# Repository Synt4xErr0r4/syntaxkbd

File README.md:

# syntaxkbd

A keyboard I made a while back.

Uses Kailh hotswap sockets with Kailh White Box V2 switches.
Standard UK QWERTY layout with 5 additional macro keys on the left (the ones where the keycaps are missing in the image below).

Also has an SK6812MINI-E addressable RGB LED for each key.

There are also four indicator LEDs (NumLock, CapsLock, ScrollLock, WinLock).
Originally, I intended to use a shift register and four discrete LEDs, but I messed up somewhere, so I bodged a WS2812B LED strip there instead.

The keycaps in the picture are from the ASUS ROG PBT Keycap Set.

The keyboard is connected via USB-C to an RP2354B microcontroller (and probably exceeds the USB standard's maximum allowed VBUS capacitance!).

The case you can see in the first image was 3D printed (PETG) in four parts.

The key placement for the PCB was done with a KiCAD extension (don't remember which one).

The keyboard is split into two PCBs: one for the keys and LEDs, and one for the controller.

Both PCBs were manufactured by JLCPCB.
I assembled the keyboard PCB (2-layer) myself, but I let JLC assemble the controller PCB (4-layer) because of the fine-pitched pins of the RP2354B.

Since the controller is an RP2354B, it can be programmed using a Raspberry Pi Debug Probe (using the SWD connector), and the firmware is written using the Raspberry Pi SDK.

I'm not quite sure what the problem is, but when I have RGB lighting effects running for a while, it starts glitching, so I usually have the LED set to static white.

Also, the firmware is not finished yet, so macros don't work yet, and lighting effects can only be reconfigured by recompiling the firmware.
It's most likely full of bugs too.
In the future, I'm also planning to have a program that can communicate with the keyboard using a vendor-specific USB interface to configure lighting effects and macros and so on.

Nonetheless, I've been using it daily for about half a year now, and it's been working great so far!

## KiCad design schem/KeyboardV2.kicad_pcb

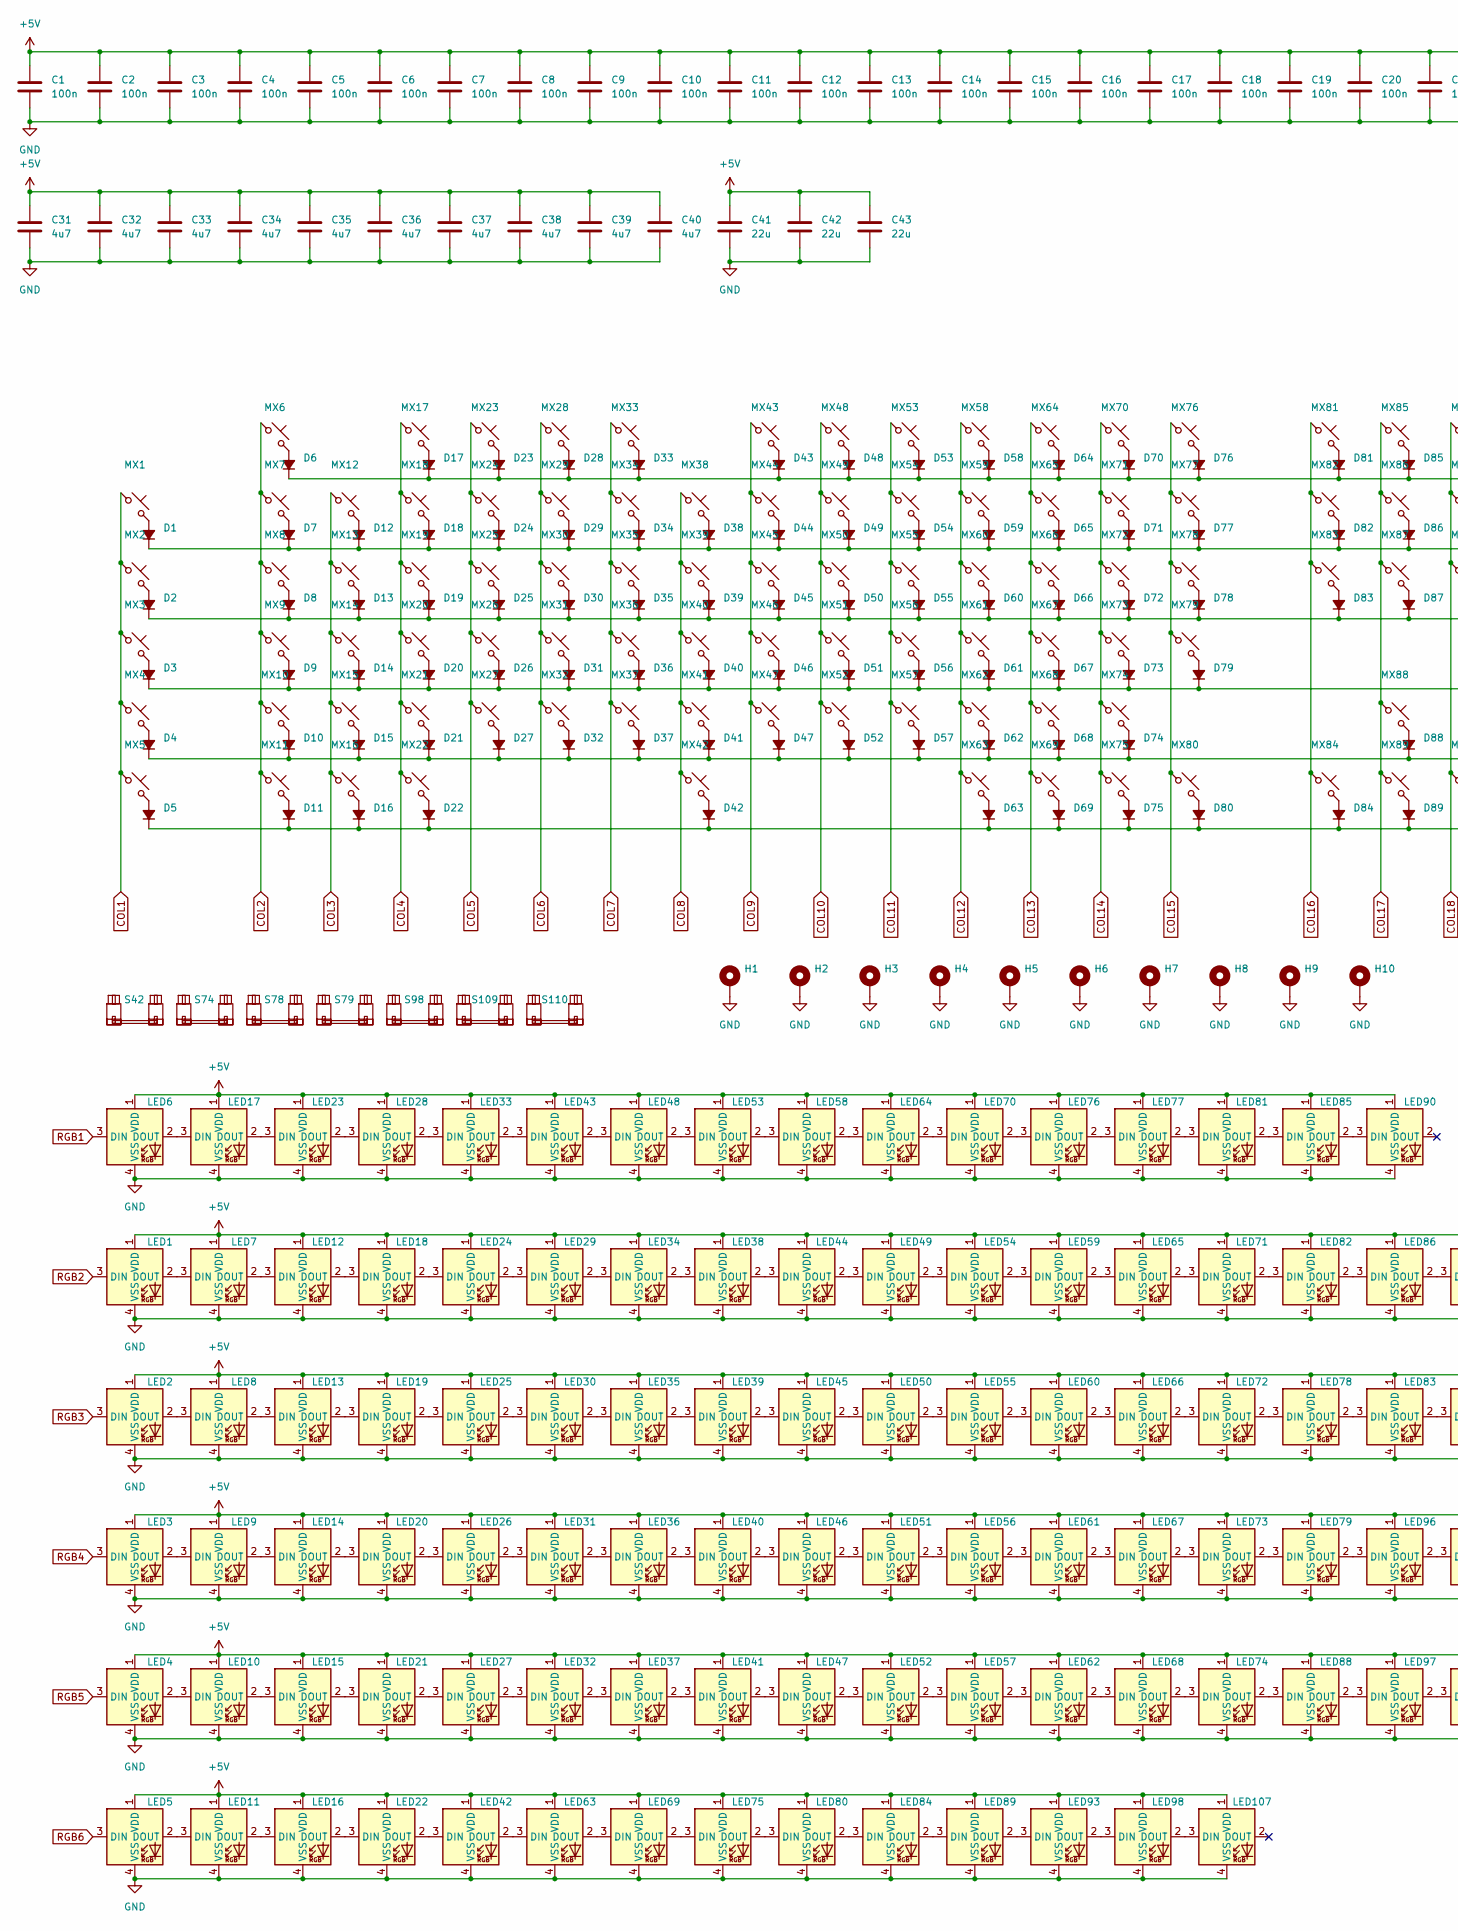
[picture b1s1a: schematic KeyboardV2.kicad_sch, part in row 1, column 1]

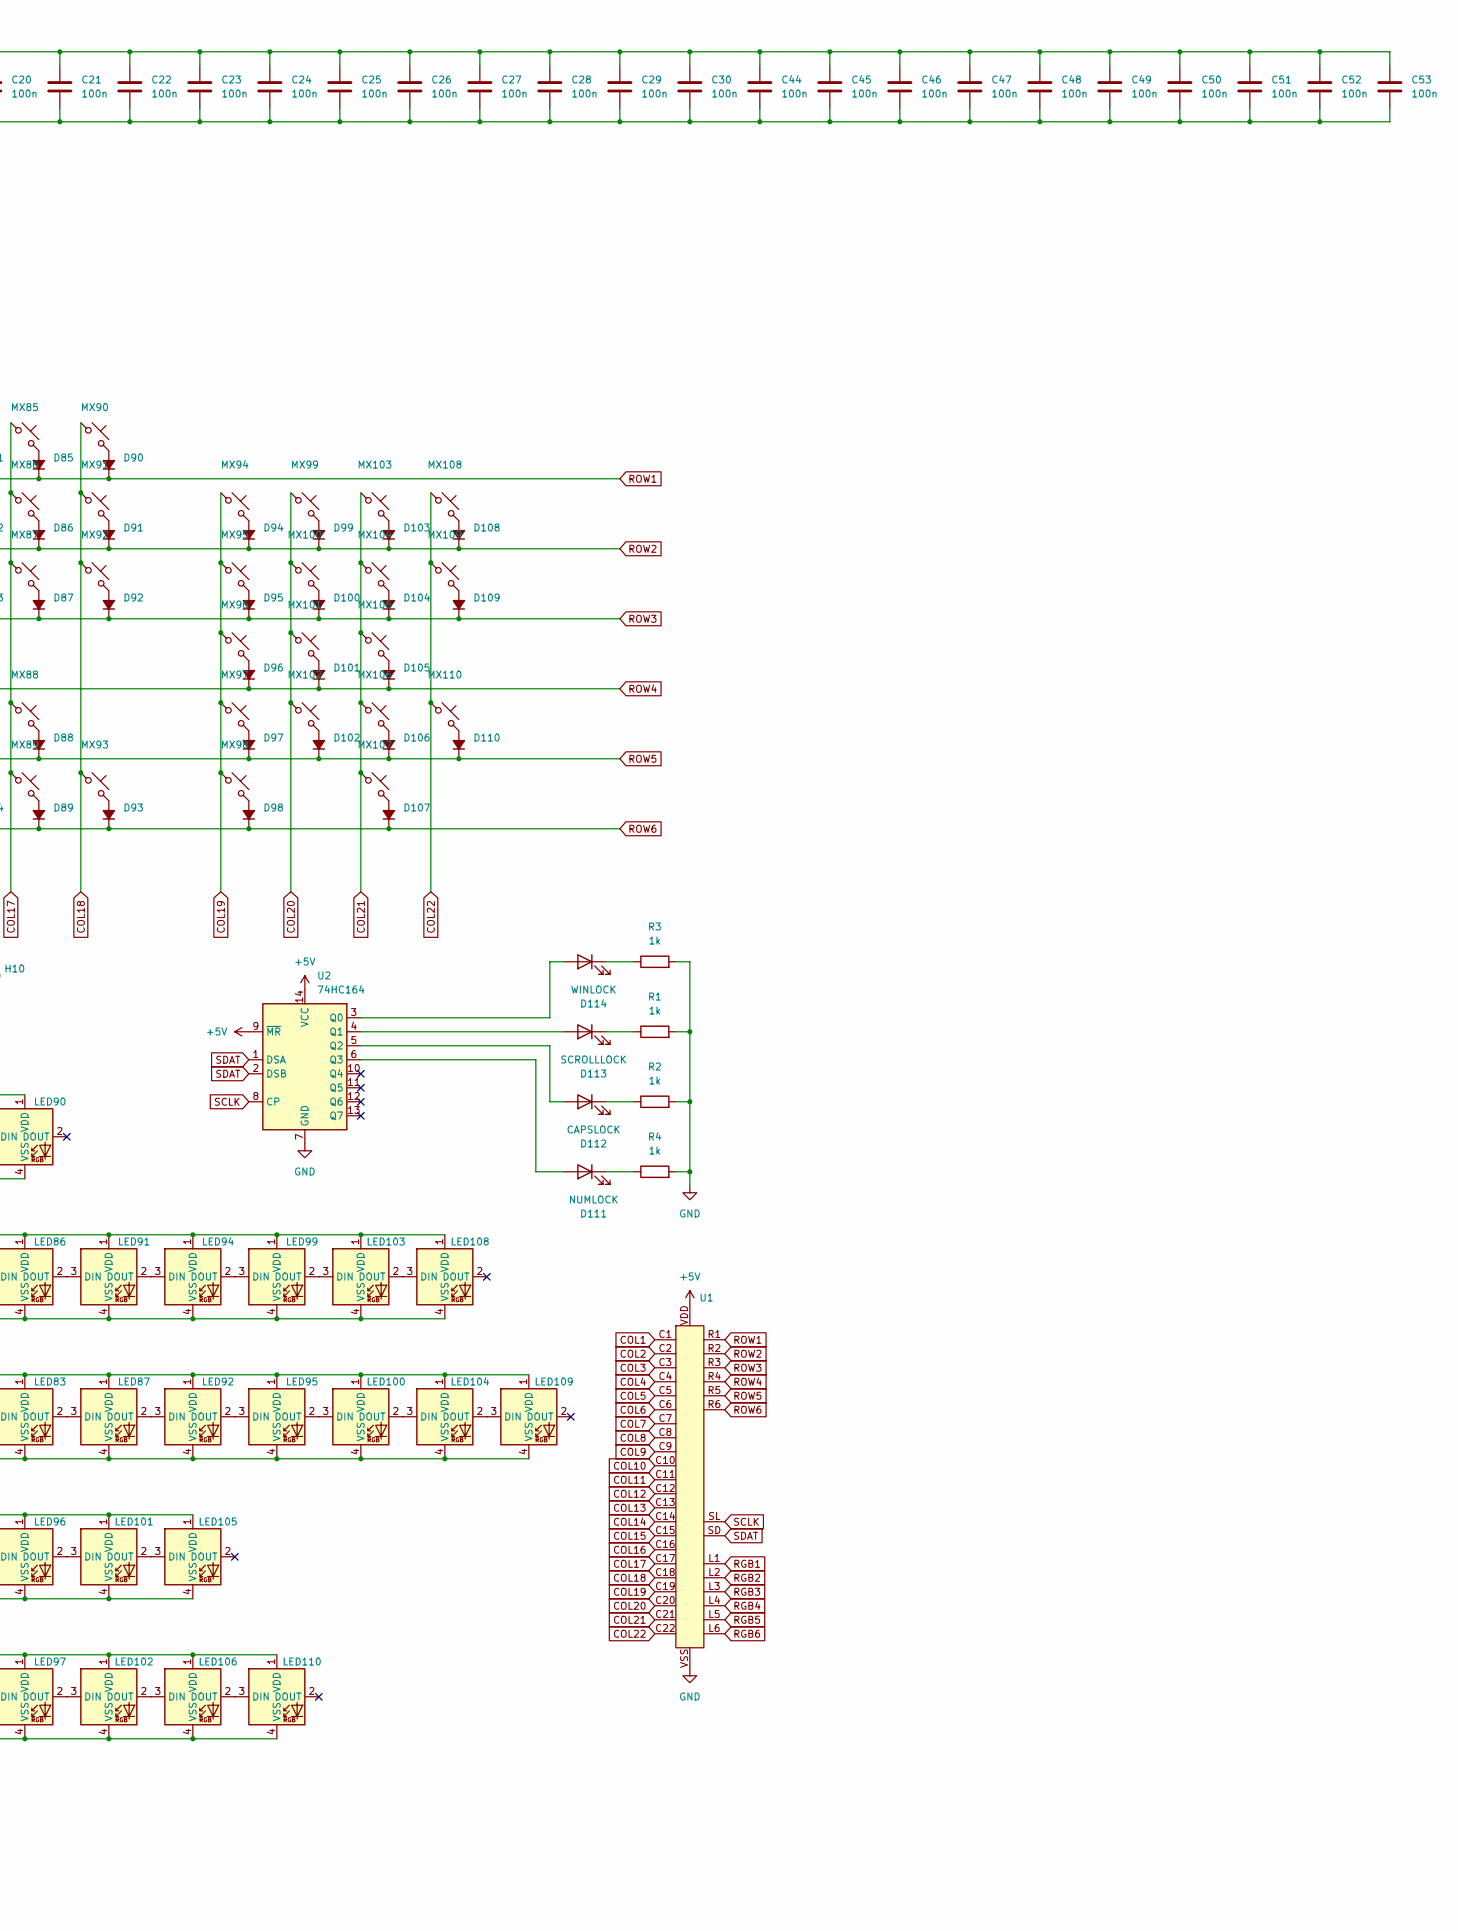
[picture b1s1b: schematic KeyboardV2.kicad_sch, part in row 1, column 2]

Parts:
C1, C2, C3, C4, C5, C6, C7, C8, C9, C10, C11, C12, C13, C14, C15, C16, C17, C18, C19, C20, C21, C22, C23, C24, C25, C26, C27, C28, C29, C30, C44, C45, C46, C47, C48, C49, C50, C51, C52, C53: 100n; C_0805_2012Metric_Pad1.18x1.45mm_HandSolder
C31, C32, C33, C34, C35, C36, C37, C38, C39, C40: 4u7; C_0805_2012Metric_Pad1.18x1.45mm_HandSolder
C41, C42, C43: 22u; C_0805_2012Metric_Pad1.18x1.45mm_HandSolder
D1, D2, D3, D4, D5, D6, D7, D8, D9, D10, D11, D12, D13, D14, D15, D16, D17, D18, D19, D20, D21, D22, D23, D24, D25, D26, D27, D28, D29, D30, D31, D32, D33, D34, D35, D36, D37, D38, D39, D40, D41, D42, D43, D44, D45, D46, D47, D48, D49, D50, D51, D52, D53, D54, D55, D56, D57, D58, D59, D60, D61, D62, D63, D64, D65, D66, D67, D68, D69, D70, D71, D72, D73, D74, D75, D76, D77, D78, D79, D80, D81, D82, D83, D84, D85, D86, D87, D88, D89, D90, D91, D92, D93, D94, D95, D96, D97, D98, D99, D100, D101, D102, D103, D104, D105, D106, D107, D108, D109, D110: D_SOD-323_HandSoldering
D111: NUMLOCK; LED_PLCC-2_3.4x3.0mm_AK
D112: CAPSLOCK; LED_PLCC-2_3.4x3.0mm_AK
D113: SCROLLLOCK; LED_PLCC-2_3.4x3.0mm_AK
D114: WINLOCK; LED_PLCC-2_3.4x3.0mm_AK
H1, H2, H3, H4, H5, H6, H7, H8, H9, H10: MountingHole_Pad; MountingHole_3.2mm_M3_DIN965_Pad_TopBottom
LED1, LED2, LED3, LED4, LED5, LED6, LED7, LED8, LED9, LED10, LED11, LED12, LED13, LED14, LED15, LED16, LED17, LED18, LED19, LED20, LED21, LED22, LED23, LED24, LED25, LED26, LED27, LED28, LED29, LED30, LED31, LED32, LED33, LED34, LED35, LED36, LED37, LED38, LED39, LED40, LED41, LED42, LED43, LED44, LED45, LED46, LED47, LED48, LED49, LED50, LED51, LED52, LED53, LED54, LED55, LED56, LED57, LED58, LED59, LED60, LED61, LED62, LED63, LED64, LED65, LED66, LED67, LED68, LED69, LED70, LED71, LED72, LED73, LED74, LED75, LED76, LED77, LED78, LED79, LED80, LED81, LED82, LED83, LED84, LED85, LED86, LED87, LED88, LED89, LED90, LED91, LED92, LED93, LED94, LED95, LED96, LED97, LED98, LED99, LED100, LED101, LED102, LED103, LED104, LED105, LED106, LED107, LED108, LED109, LED110: MX_SK6812MINI-E; LED_MX_6028R
MX1, MX2, MX3, MX4, MX5, MX6, MX7, MX8, MX9, MX10, MX11, MX12, MX13, MX14, MX15, MX16, MX17, MX18, MX19, MX20, MX21, MX22, MX23, MX24, MX25, MX26, MX27, MX28, MX29, MX30, MX31, MX32, MX33, MX34, MX35, MX36, MX37, MX38, MX39, MX40, MX41, MX42, MX43, MX44, MX45, MX46, MX47, MX48, MX49, MX50, MX51, MX52, MX53, MX54, MX55, MX56, MX57, MX58, MX59, MX60, MX61, MX62, MX63, MX64, MX65, MX66, MX67, MX68, MX69, MX70, MX71, MX72, MX73, MX74, MX75, MX76, MX77, MX78, MX79, MX80, MX81, MX82, MX83, MX84, MX85, MX86, MX87, MX88, MX89, MX90, MX91, MX92, MX93, MX94, MX95, MX96, MX97, MX98, MX99, MX100, MX101, MX102, MX103, MX104, MX105, MX106, MX107, MX108, MX109, MX110: SW_MX_HS_CPG151101S11_1u
R1, R2, R3, R4: 1k; R_0402_1005Metric_Pad0.72x0.64mm_HandSolder
S42: MX_stab; STAB_MX_P_6.25u
S74: MX_stab; STAB_MX_P_2.75u
S78, S98, S109, S110: MX_stab; STAB_MX_P_2u
S79: MX_stab; STAB_MX_P_ISO
U1: KBDCTRL_Conn
U2: 74HC164; SOIC-14_3.9x8.7mm_P1.27mm

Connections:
+5V: C1.1, C2.1, C3.1, C4.1, C5.1, C6.1, C7.1, C8.1, C9.1, C10.1, C11.1, C12.1, C13.1, C14.1, C15.1, C16.1, C17.1, C18.1, C19.1, C20.1, C21.1, C22.1, C23.1, C24.1, C25.1, C26.1, C27.1, C28.1, C29.1, C30.1, C31.1, C32.1, C33.1, C34.1, C35.1, C36.1, C37.1, C38.1, C39.1, C40.1, C41.1, C42.1, C43.1, C44.1, C45.1, C46.1, C47.1, C48.1, C49.1, C50.1, C51.1, C52.1, C53.1, LED1.1 (VDD), LED2.1 (VDD), LED3.1 (VDD), LED4.1 (VDD), LED5.1 (VDD), LED6.1 (VDD), LED7.1 (VDD), LED8.1 (VDD), LED9.1 (VDD), LED10.1 (VDD), LED11.1 (VDD), LED12.1 (VDD), LED13.1 (VDD), LED14.1 (VDD), LED15.1 (VDD), LED16.1 (VDD), LED17.1 (VDD), LED18.1 (VDD), LED19.1 (VDD), LED20.1 (VDD), LED21.1 (VDD), LED22.1 (VDD), LED23.1 (VDD), LED24.1 (VDD), LED25.1 (VDD), LED26.1 (VDD), LED27.1 (VDD), LED28.1 (VDD), LED29.1 (VDD), LED30.1 (VDD), LED31.1 (VDD), LED32.1 (VDD), LED33.1 (VDD), LED34.1 (VDD), LED35.1 (VDD), LED36.1 (VDD), LED37.1 (VDD), LED38.1 (VDD), LED39.1 (VDD), LED40.1 (VDD), LED41.1 (VDD), LED42.1 (VDD), LED43.1 (VDD), LED44.1 (VDD), LED45.1 (VDD), LED46.1 (VDD), LED47.1 (VDD), LED48.1 (VDD), LED49.1 (VDD), LED50.1 (VDD), LED51.1 (VDD), LED52.1 (VDD), LED53.1 (VDD), LED54.1 (VDD), LED55.1 (VDD), LED56.1 (VDD), LED57.1 (VDD), LED58.1 (VDD), LED59.1 (VDD), LED60.1 (VDD), LED61.1 (VDD), LED62.1 (VDD), LED63.1 (VDD), LED64.1 (VDD), LED65.1 (VDD), LED66.1 (VDD), LED67.1 (VDD), LED68.1 (VDD), LED69.1 (VDD), LED70.1 (VDD), LED71.1 (VDD), LED72.1 (VDD), LED73.1 (VDD), LED74.1 (VDD), LED75.1 (VDD), LED76.1 (VDD), LED77.1 (VDD), LED78.1 (VDD), LED79.1 (VDD), LED80.1 (VDD), LED81.1 (VDD), LED82.1 (VDD), LED83.1 (VDD), LED84.1 (VDD), LED85.1 (VDD), LED86.1 (VDD), LED87.1 (VDD), LED88.1 (VDD), LED89.1 (VDD), LED90.1 (VDD), LED91.1 (VDD), LED92.1 (VDD), LED93.1 (VDD), LED94.1 (VDD), LED95.1 (VDD), LED96.1 (VDD), LED97.1 (VDD), LED98.1 (VDD), LED99.1 (VDD), LED100.1 (VDD), LED101.1 (VDD), LED102.1 (VDD), LED103.1 (VDD), LED104.1 (VDD), LED105.1 (VDD), LED106.1 (VDD), LED107.1 (VDD), LED108.1 (VDD), LED109.1 (VDD), LED110.1 (VDD), U1.VDD, U2.9 (~MR), U2.14 (VCC)
COL1: MX1.1, MX2.1, MX3.1, MX4.1, MX5.1, U1.C1
COL2: MX6.1, MX7.1, MX8.1, MX9.1, MX10.1, MX11.1, U1.C2
COL3: MX12.1, MX13.1, MX14.1, MX15.1, MX16.1, U1.C3
COL4: MX17.1, MX18.1, MX19.1, MX20.1, MX21.1, MX22.1, U1.C4
COL5: MX23.1, MX24.1, MX25.1, MX26.1, MX27.1, U1.C5
COL6: MX28.1, MX29.1, MX30.1, MX31.1, MX32.1, U1.C6
COL7: MX33.1, MX34.1, MX35.1, MX36.1, MX37.1, U1.C7
COL8: MX38.1, MX39.1, MX40.1, MX41.1, MX42.1, U1.C8
COL9: MX43.1, MX44.1, MX45.1, MX46.1, MX47.1, U1.C9
COL10: MX48.1, MX49.1, MX50.1, MX51.1, MX52.1, U1.C10
COL11: MX53.1, MX54.1, MX55.1, MX56.1, MX57.1, U1.C11
COL12: MX58.1, MX59.1, MX60.1, MX61.1, MX62.1, MX63.1, U1.C12
COL13: MX64.1, MX65.1, MX66.1, MX67.1, MX68.1, MX69.1, U1.C13
COL14: MX70.1, MX71.1, MX72.1, MX73.1, MX74.1, MX75.1, U1.C14
COL15: MX76.1, MX77.1, MX78.1, MX79.1, MX80.1, U1.C15
COL16: MX81.1, MX82.1, MX83.1, MX84.1, U1.C16
COL17: MX85.1, MX86.1, MX87.1, MX88.1, MX89.1, U1.C17
COL18: MX90.1, MX91.1, MX92.1, MX93.1, U1.C18
COL19: MX94.1, MX95.1, MX96.1, MX97.1, MX98.1, U1.C19
COL20: MX99.1, MX100.1, MX101.1, MX102.1, U1.C20
COL21: MX103.1, MX104.1, MX105.1, MX106.1, MX107.1, U1.C21
COL22: MX108.1, MX109.1, MX110.1, U1.C22
GND: C1.2, C2.2, C3.2, C4.2, C5.2, C6.2, C7.2, C8.2, C9.2, C10.2, C11.2, C12.2, C13.2, C14.2, C15.2, C16.2, C17.2, C18.2, C19.2, C20.2, C21.2, C22.2, C23.2, C24.2, C25.2, C26.2, C27.2, C28.2, C29.2, C30.2, C31.2, C32.2, C33.2, C34.2, C35.2, C36.2, C37.2, C38.2, C39.2, C40.2, C41.2, C42.2, C43.2, C44.2, C45.2, C46.2, C47.2, C48.2, C49.2, C50.2, C51.2, C52.2, C53.2, H1.1, H2.1, H3.1, H4.1, H5.1, H6.1, H7.1, H8.1, H9.1, H10.1, LED1.4 (VSS), LED2.4 (VSS), LED3.4 (VSS), LED4.4 (VSS), LED5.4 (VSS), LED6.4 (VSS), LED7.4 (VSS), LED8.4 (VSS), LED9.4 (VSS), LED10.4 (VSS), LED11.4 (VSS), LED12.4 (VSS), LED13.4 (VSS), LED14.4 (VSS), LED15.4 (VSS), LED16.4 (VSS), LED17.4 (VSS), LED18.4 (VSS), LED19.4 (VSS), LED20.4 (VSS), LED21.4 (VSS), LED22.4 (VSS), LED23.4 (VSS), LED24.4 (VSS), LED25.4 (VSS), LED26.4 (VSS), LED27.4 (VSS), LED28.4 (VSS), LED29.4 (VSS), LED30.4 (VSS), LED31.4 (VSS), LED32.4 (VSS), LED33.4 (VSS), LED34.4 (VSS), LED35.4 (VSS), LED36.4 (VSS), LED37.4 (VSS), LED38.4 (VSS), LED39.4 (VSS), LED40.4 (VSS), LED41.4 (VSS), LED42.4 (VSS), LED43.4 (VSS), LED44.4 (VSS), LED45.4 (VSS), LED46.4 (VSS), LED47.4 (VSS), LED48.4 (VSS), LED49.4 (VSS), LED50.4 (VSS), LED51.4 (VSS), LED52.4 (VSS), LED53.4 (VSS), LED54.4 (VSS), LED55.4 (VSS), LED56.4 (VSS), LED57.4 (VSS), LED58.4 (VSS), LED59.4 (VSS), LED60.4 (VSS), LED61.4 (VSS), LED62.4 (VSS), LED63.4 (VSS), LED64.4 (VSS), LED65.4 (VSS), LED66.4 (VSS), LED67.4 (VSS), LED68.4 (VSS), LED69.4 (VSS), LED70.4 (VSS), LED71.4 (VSS), LED72.4 (VSS), LED73.4 (VSS), LED74.4 (VSS), LED75.4 (VSS), LED76.4 (VSS), LED77.4 (VSS), LED78.4 (VSS), LED79.4 (VSS), LED80.4 (VSS), LED81.4 (VSS), LED82.4 (VSS), LED83.4 (VSS), LED84.4 (VSS), LED85.4 (VSS), LED86.4 (VSS), LED87.4 (VSS), LED88.4 (VSS), LED89.4 (VSS), LED90.4 (VSS), LED91.4 (VSS), LED92.4 (VSS), LED93.4 (VSS), LED94.4 (VSS), LED95.4 (VSS), LED96.4 (VSS), LED97.4 (VSS), LED98.4 (VSS), LED99.4 (VSS), LED100.4 (VSS), LED101.4 (VSS), LED102.4 (VSS), LED103.4 (VSS), LED104.4 (VSS), LED105.4 (VSS), LED106.4 (VSS), LED107.4 (VSS), LED108.4 (VSS), LED109.4 (VSS), LED110.4 (VSS), R1.2, R2.2, R3.2, R4.2, U1.VSS, U2.7 (GND)
unnamed: D1.2 (A), MX1.2
unnamed: D2.2 (A), MX2.2
unnamed: D3.2 (A), MX3.2
unnamed: D4.2 (A), MX4.2
unnamed: D5.2 (A), MX5.2
unnamed: D6.2 (A), MX6.2
unnamed: D7.2 (A), MX7.2
unnamed: D8.2 (A), MX8.2
unnamed: D9.2 (A), MX9.2
unnamed: D10.2 (A), MX10.2
unnamed: D11.2 (A), MX11.2
unnamed: D12.2 (A), MX12.2
unnamed: D13.2 (A), MX13.2
unnamed: D14.2 (A), MX14.2
unnamed: D15.2 (A), MX15.2
unnamed: D16.2 (A), MX16.2
unnamed: D17.2 (A), MX17.2
unnamed: D18.2 (A), MX18.2
unnamed: D19.2 (A), MX19.2
unnamed: D20.2 (A), MX20.2
unnamed: D21.2 (A), MX21.2
unnamed: D22.2 (A), MX22.2
unnamed: D23.2 (A), MX23.2
unnamed: D24.2 (A), MX24.2
unnamed: D25.2 (A), MX25.2
unnamed: D26.2 (A), MX26.2
unnamed: D27.2 (A), MX27.2
unnamed: D28.2 (A), MX28.2
unnamed: D29.2 (A), MX29.2
unnamed: D30.2 (A), MX30.2
unnamed: D31.2 (A), MX31.2
unnamed: D32.2 (A), MX32.2
unnamed: D33.2 (A), MX33.2
unnamed: D34.2 (A), MX34.2
unnamed: D35.2 (A), MX35.2
unnamed: D36.2 (A), MX36.2
unnamed: D37.2 (A), MX37.2
unnamed: D38.2 (A), MX38.2
unnamed: D39.2 (A), MX39.2
unnamed: D40.2 (A), MX40.2
unnamed: D41.2 (A), MX41.2
unnamed: D42.2 (A), MX42.2
unnamed: D43.2 (A), MX43.2
unnamed: D44.2 (A), MX44.2
unnamed: D45.2 (A), MX45.2
unnamed: D46.2 (A), MX46.2
unnamed: D47.2 (A), MX47.2
unnamed: D48.2 (A), MX48.2
unnamed: D49.2 (A), MX49.2
unnamed: D50.2 (A), MX50.2
unnamed: D51.2 (A), MX51.2
unnamed: D52.2 (A), MX52.2
unnamed: D53.2 (A), MX53.2
unnamed: D54.2 (A), MX54.2
unnamed: D55.2 (A), MX55.2
unnamed: D56.2 (A), MX56.2
unnamed: D57.2 (A), MX57.2
unnamed: D58.2 (A), MX58.2
unnamed: D59.2 (A), MX59.2
unnamed: D60.2 (A), MX60.2
unnamed: D61.2 (A), MX61.2
unnamed: D62.2 (A), MX62.2
unnamed: D63.2 (A), MX63.2
unnamed: D64.2 (A), MX64.2
unnamed: D65.2 (A), MX65.2
unnamed: D66.2 (A), MX66.2
unnamed: D67.2 (A), MX67.2
unnamed: D68.2 (A), MX68.2
unnamed: D69.2 (A), MX69.2
unnamed: D70.2 (A), MX70.2
unnamed: D71.2 (A), MX71.2
unnamed: D72.2 (A), MX72.2
unnamed: D73.2 (A), MX73.2
unnamed: D74.2 (A), MX74.2
unnamed: D75.2 (A), MX75.2
unnamed: D76.2 (A), MX76.2
unnamed: D77.2 (A), MX77.2
unnamed: D78.2 (A), MX78.2
unnamed: D79.2 (A), MX79.2
unnamed: D80.2 (A), MX80.2
unnamed: D81.2 (A), MX81.2
unnamed: D82.2 (A), MX82.2
unnamed: D83.2 (A), MX83.2
unnamed: D84.2 (A), MX84.2
unnamed: D85.2 (A), MX85.2
unnamed: D86.2 (A), MX86.2
unnamed: D87.2 (A), MX87.2
unnamed: D88.2 (A), MX88.2
unnamed: D89.2 (A), MX89.2
unnamed: D90.2 (A), MX90.2
unnamed: D91.2 (A), MX91.2
unnamed: D92.2 (A), MX92.2
unnamed: D93.2 (A), MX93.2
unnamed: D94.2 (A), MX94.2
unnamed: D95.2 (A), MX95.2
unnamed: D96.2 (A), MX96.2
unnamed: D97.2 (A), MX97.2
unnamed: D98.2 (A), MX98.2
unnamed: D99.2 (A), MX99.2
unnamed: D100.2 (A), MX100.2
unnamed: D101.2 (A), MX101.2
unnamed: D102.2 (A), MX102.2
unnamed: D103.2 (A), MX103.2
unnamed: D104.2 (A), MX104.2
unnamed: D105.2 (A), MX105.2
unnamed: D106.2 (A), MX106.2
unnamed: D107.2 (A), MX107.2
unnamed: D108.2 (A), MX108.2
unnamed: D109.2 (A), MX109.2
unnamed: D110.2 (A), MX110.2
unnamed: D111.2 (A), U2.6 (Q3)
unnamed: D111.1 (K), R4.1
unnamed: D112.2 (A), U2.5 (Q2)
unnamed: D112.1 (K), R2.1
unnamed: D113.2 (A), U2.4 (Q1)
unnamed: D113.1 (K), R1.1
unnamed: D114.2 (A), U2.3 (Q0)
unnamed: D114.1 (K), R3.1
unnamed: LED1.2 (DOUT), LED7.3 (DIN)
unnamed: LED2.2 (DOUT), LED8.3 (DIN)
unnamed: LED3.2 (DOUT), LED9.3 (DIN)
unnamed: LED4.2 (DOUT), LED10.3 (DIN)
unnamed: LED10.2 (DOUT), LED15.3 (DIN)
unnamed: LED5.2 (DOUT), LED11.3 (DIN)
unnamed: LED11.2 (DOUT), LED16.3 (DIN)
unnamed: LED7.2 (DOUT), LED12.3 (DIN)
unnamed: LED12.2 (DOUT), LED18.3 (DIN)
unnamed: LED8.2 (DOUT), LED13.3 (DIN)
unnamed: LED13.2 (DOUT), LED19.3 (DIN)
unnamed: LED9.2 (DOUT), LED14.3 (DIN)
unnamed: LED14.2 (DOUT), LED20.3 (DIN)
unnamed: LED15.2 (DOUT), LED21.3 (DIN)
unnamed: LED16.2 (DOUT), LED22.3 (DIN)
unnamed: LED6.2 (DOUT), LED17.3 (DIN)
unnamed: LED17.2 (DOUT), LED23.3 (DIN)
unnamed: LED18.2 (DOUT), LED24.3 (DIN)
unnamed: LED19.2 (DOUT), LED25.3 (DIN)
unnamed: LED20.2 (DOUT), LED26.3 (DIN)
unnamed: LED21.2 (DOUT), LED27.3 (DIN)
unnamed: LED22.2 (DOUT), LED42.3 (DIN)
unnamed: LED23.2 (DOUT), LED28.3 (DIN)
unnamed: LED24.2 (DOUT), LED29.3 (DIN)
unnamed: LED25.2 (DOUT), LED30.3 (DIN)
unnamed: LED26.2 (DOUT), LED31.3 (DIN)
unnamed: LED27.2 (DOUT), LED32.3 (DIN)
unnamed: LED28.2 (DOUT), LED33.3 (DIN)
unnamed: LED29.2 (DOUT), LED34.3 (DIN)
unnamed: LED30.2 (DOUT), LED35.3 (DIN)
unnamed: LED31.2 (DOUT), LED36.3 (DIN)
unnamed: LED32.2 (DOUT), LED37.3 (DIN)
unnamed: LED33.2 (DOUT), LED43.3 (DIN)
unnamed: LED34.2 (DOUT), LED38.3 (DIN)
unnamed: LED35.2 (DOUT), LED39.3 (DIN)
unnamed: LED36.2 (DOUT), LED40.3 (DIN)
unnamed: LED37.2 (DOUT), LED41.3 (DIN)
unnamed: LED38.2 (DOUT), LED44.3 (DIN)
unnamed: LED39.2 (DOUT), LED45.3 (DIN)
unnamed: LED40.2 (DOUT), LED46.3 (DIN)
unnamed: LED41.2 (DOUT), LED47.3 (DIN)
unnamed: LED42.2 (DOUT), LED63.3 (DIN)
unnamed: LED43.2 (DOUT), LED48.3 (DIN)
unnamed: LED44.2 (DOUT), LED49.3 (DIN)
unnamed: LED45.2 (DOUT), LED50.3 (DIN)
unnamed: LED46.2 (DOUT), LED51.3 (DIN)
unnamed: LED47.2 (DOUT), LED52.3 (DIN)
unnamed: LED48.2 (DOUT), LED53.3 (DIN)
unnamed: LED49.2 (DOUT), LED54.3 (DIN)
unnamed: LED50.2 (DOUT), LED55.3 (DIN)
unnamed: LED51.2 (DOUT), LED56.3 (DIN)
unnamed: LED52.2 (DOUT), LED57.3 (DIN)
unnamed: LED53.2 (DOUT), LED58.3 (DIN)
unnamed: LED54.2 (DOUT), LED59.3 (DIN)
unnamed: LED55.2 (DOUT), LED60.3 (DIN)
unnamed: LED56.2 (DOUT), LED61.3 (DIN)
unnamed: LED57.2 (DOUT), LED62.3 (DIN)
unnamed: LED58.2 (DOUT), LED64.3 (DIN)
unnamed: LED59.2 (DOUT), LED65.3 (DIN)
unnamed: LED60.2 (DOUT), LED66.3 (DIN)
unnamed: LED61.2 (DOUT), LED67.3 (DIN)
unnamed: LED62.2 (DOUT), LED68.3 (DIN)
unnamed: LED63.2 (DOUT), LED69.3 (DIN)
unnamed: LED64.2 (DOUT), LED70.3 (DIN)
unnamed: LED65.2 (DOUT), LED71.3 (DIN)
unnamed: LED66.2 (DOUT), LED72.3 (DIN)
unnamed: LED67.2 (DOUT), LED73.3 (DIN)
unnamed: LED68.2 (DOUT), LED74.3 (DIN)
unnamed: LED69.2 (DOUT), LED75.3 (DIN)
unnamed: LED70.2 (DOUT), LED76.3 (DIN)
unnamed: LED71.2 (DOUT), LED82.3 (DIN)
unnamed: LED72.2 (DOUT), LED78.3 (DIN)
unnamed: LED73.2 (DOUT), LED79.3 (DIN)
unnamed: LED74.2 (DOUT), LED88.3 (DIN)
unnamed: LED75.2 (DOUT), LED80.3 (DIN)
unnamed: LED76.2 (DOUT), LED77.3 (DIN)
unnamed: LED77.2 (DOUT), LED81.3 (DIN)
unnamed: LED78.2 (DOUT), LED83.3 (DIN)
unnamed: LED79.2 (DOUT), LED96.3 (DIN)
unnamed: LED80.2 (DOUT), LED84.3 (DIN)
unnamed: LED81.2 (DOUT), LED85.3 (DIN)
unnamed: LED82.2 (DOUT), LED86.3 (DIN)
unnamed: LED83.2 (DOUT), LED87.3 (DIN)
unnamed: LED84.2 (DOUT), LED89.3 (DIN)
unnamed: LED85.2 (DOUT), LED90.3 (DIN)
unnamed: LED86.2 (DOUT), LED91.3 (DIN)
unnamed: LED87.2 (DOUT), LED92.3 (DIN)
unnamed: LED88.2 (DOUT), LED97.3 (DIN)
unnamed: LED89.2 (DOUT), LED93.3 (DIN)
unnamed: LED91.2 (DOUT), LED94.3 (DIN)
unnamed: LED92.2 (DOUT), LED95.3 (DIN)
unnamed: LED93.2 (DOUT), LED98.3 (DIN)
unnamed: LED94.2 (DOUT), LED99.3 (DIN)
unnamed: LED95.2 (DOUT), LED100.3 (DIN)
unnamed: LED100.2 (DOUT), LED104.3 (DIN)
unnamed: LED96.2 (DOUT), LED101.3 (DIN)
unnamed: LED101.2 (DOUT), LED105.3 (DIN)
unnamed: LED97.2 (DOUT), LED102.3 (DIN)
unnamed: LED102.2 (DOUT), LED106.3 (DIN)
unnamed: LED99.2 (DOUT), LED103.3 (DIN)
unnamed: LED103.2 (DOUT), LED108.3 (DIN)
unnamed: LED104.2 (DOUT), LED109.3 (DIN)
unnamed: LED106.2 (DOUT), LED110.3 (DIN)
unnamed: LED98.2 (DOUT), LED107.3 (DIN)
RGB1: LED6.3 (DIN), U1.L1
RGB2: LED1.3 (DIN), U1.L2
RGB3: LED2.3 (DIN), U1.L3
RGB4: LED3.3 (DIN), U1.L4
RGB5: LED4.3 (DIN), U1.L5
RGB6: LED5.3 (DIN), U1.L6
ROW1: D6.1 (K), D17.1 (K), D23.1 (K), D28.1 (K), D33.1 (K), D43.1 (K), D48.1 (K), D53.1 (K), D58.1 (K), D64.1 (K), D70.1 (K), D76.1 (K), D81.1 (K), D85.1 (K), D90.1 (K), U1.R1
ROW2: D1.1 (K), D7.1 (K), D12.1 (K), D18.1 (K), D24.1 (K), D29.1 (K), D34.1 (K), D38.1 (K), D44.1 (K), D49.1 (K), D54.1 (K), D59.1 (K), D65.1 (K), D71.1 (K), D77.1 (K), D82.1 (K), D86.1 (K), D91.1 (K), D94.1 (K), D99.1 (K), D103.1 (K), D108.1 (K), U1.R2
ROW3: D2.1 (K), D8.1 (K), D13.1 (K), D19.1 (K), D25.1 (K), D30.1 (K), D35.1 (K), D39.1 (K), D45.1 (K), D50.1 (K), D55.1 (K), D60.1 (K), D66.1 (K), D72.1 (K), D78.1 (K), D83.1 (K), D87.1 (K), D92.1 (K), D95.1 (K), D100.1 (K), D104.1 (K), D109.1 (K), U1.R3
ROW4: D3.1 (K), D9.1 (K), D14.1 (K), D20.1 (K), D26.1 (K), D31.1 (K), D36.1 (K), D40.1 (K), D46.1 (K), D51.1 (K), D56.1 (K), D61.1 (K), D67.1 (K), D73.1 (K), D79.1 (K), D96.1 (K), D101.1 (K), D105.1 (K), U1.R4
ROW5: D4.1 (K), D10.1 (K), D15.1 (K), D21.1 (K), D27.1 (K), D32.1 (K), D37.1 (K), D41.1 (K), D47.1 (K), D52.1 (K), D57.1 (K), D62.1 (K), D68.1 (K), D74.1 (K), D88.1 (K), D97.1 (K), D102.1 (K), D106.1 (K), D110.1 (K), U1.R5
ROW6: D5.1 (K), D11.1 (K), D16.1 (K), D22.1 (K), D42.1 (K), D63.1 (K), D69.1 (K), D75.1 (K), D80.1 (K), D84.1 (K), D89.1 (K), D93.1 (K), D98.1 (K), D107.1 (K), U1.R6
SCLK: U1.SL, U2.8 (CP)
SDAT: U1.SD, U2.1 (DSA), U2.2 (DSB)

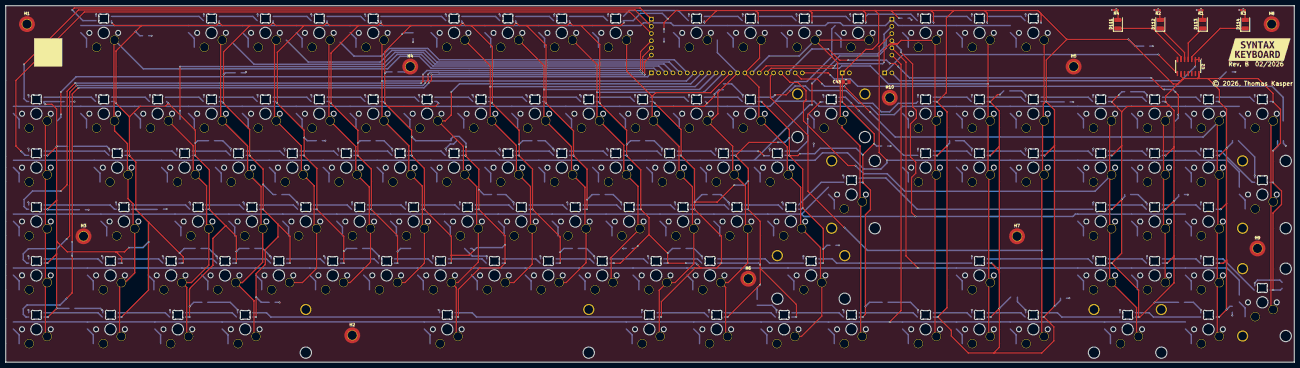
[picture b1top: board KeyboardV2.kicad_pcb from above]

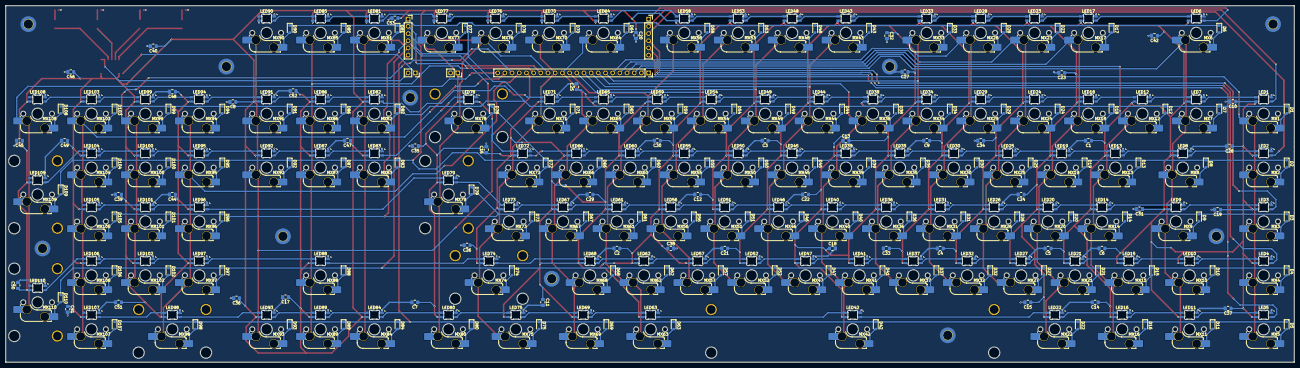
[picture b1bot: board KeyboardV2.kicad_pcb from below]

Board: 2 copper layers, 455.5 x 126.0 mm, 411 parts (382 on the bottom side), 260 nets.

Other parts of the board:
kibuzzard-699F618B: G***; kibuzzard-699F618B

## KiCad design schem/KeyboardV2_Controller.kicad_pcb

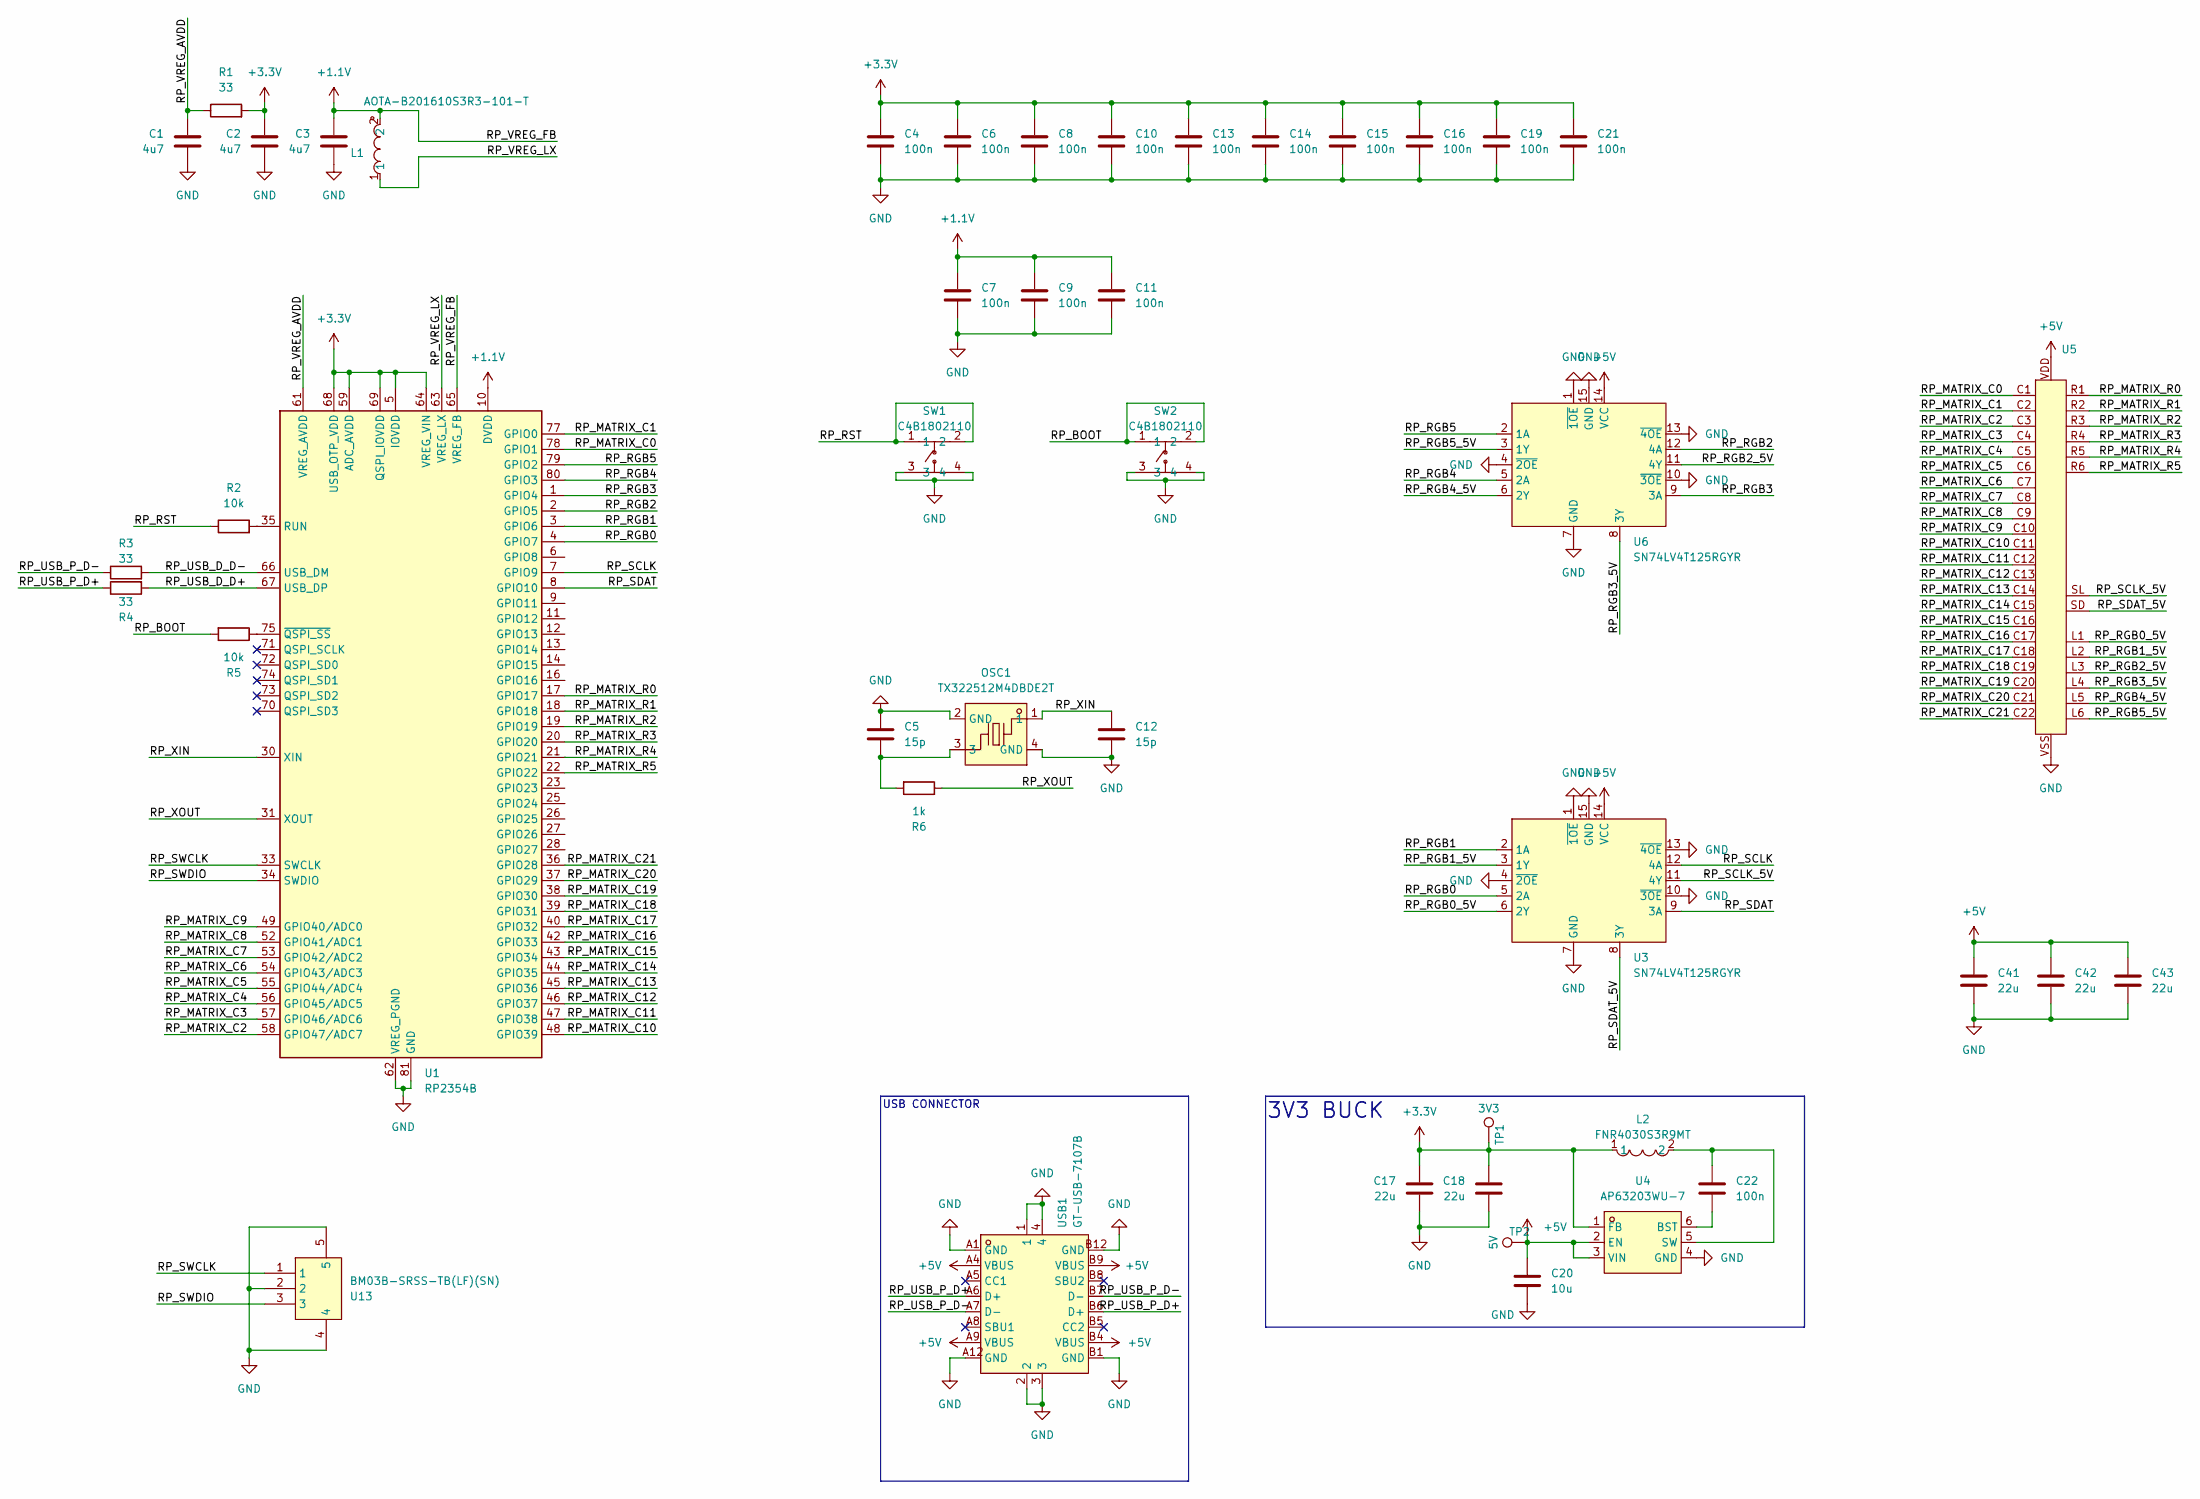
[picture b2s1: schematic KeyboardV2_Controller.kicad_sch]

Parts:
C1, C2, C3: 4u7; C_0402_1005Metric; LCSC Part C368809
C4, C6, C7, C8, C9, C10, C11, C13, C14, C15, C16, C19, C21, C22: 100n; C_0402_1005Metric; LCSC Part C60474
C5, C12: 15p; C_0402_1005Metric; LCSC Part C326803
C17, C18: 22u; C_1206_3216Metric; LCSC Part C12891
C20: 10u; C_0805_2012Metric; LCSC Part C15850
C41, C42, C43: 22u; C_0805_2012Metric; LCSC Part C602037
L1: AOTA-B201610S3R3-101-T; IND-SMD_L2.0-W1.6_AOTA-B201610S3R3-101-T; LCSC Part C42411119
L2: FNR4030S3R9MT; IND-SMD_L4.0-W4.0_FNR40XXS; LCSC Part C167872
OSC1: TX322512M4DBDE2T; OSC-SMD_4P-L3.2-W2.5-BL; LCSC Part C5310728
R1, R3, R4: 33; R_0402_1005Metric; LCSC Part C7273719
R2, R5: 10k; R_0402_1005Metric; LCSC Part C60490
R6: 1k; R_0402_1005Metric; LCSC Part C106235
SW1, SW2: C4B1802110; SW-SMD_4P-L3.5-W3.0-P1.50-LS4.7; LCSC Part C49393608
TP1: 3V3; TestPoint_Pad_D2.0mm
TP2: 5V; TestPoint_Pad_D2.0mm
U1: RP2354B; QFN-80-1EP_10x10mm_P0.4mm_EP3.4x3.4mm; LCSC Part C39843328
U3, U6: SN74LV4T125RGYR; VQFN-14_L3.5-W3.5-P0.50-BL-EP; LCSC Part C411879
U4: AP63203WU-7; TSOT-26_L2.9-W1.6-P0.95-LS2.8-BL; LCSC Part C780769
U5: KBDCTRL_Conn
U13: BM03B-SRSS-TB(LF)(SN); CONN-SMD-3P-P1.00_BM03B-SRSS-TB-LF-SN; LCSC Part C160389
USB1: GT-USB-7107B; USB-C-TH_GT-USB-7107B; LCSC Part C49302689

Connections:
+1.1V: C3.1, C7.1, C9.1, C11.1, L1.2, U1.10 (DVDD), U1.32 (DVDD), U1.51 (DVDD), U1.65 (VREG_FB)
+3.3V: C2.1, C4.1, C6.1, C8.1, C10.1, C13.1, C14.1, C15.1, C16.1, C17.1, C18.1, C19.1, C21.1, L2.1, R1.2, TP1.1, U1.5 (IOVDD), U1.15 (IOVDD), U1.24 (IOVDD), U1.29 (IOVDD), U1.41 (IOVDD), U1.50 (IOVDD), U1.59 (ADC_AVDD), U1.60 (IOVDD), U1.64 (VREG_VIN), U1.68 (USB_OTP_VDD), U1.69 (QSPI_IOVDD), U1.76 (IOVDD), U4.1 (FB)
+5V: C20.1, C41.1, C42.1, C43.1, TP2.1, U3.14 (VCC), U4.2 (EN), U4.3 (VIN), U5.VDD, U6.14 (VCC), USB1.A4 (VBUS), USB1.A9 (VBUS), USB1.B4 (VBUS), USB1.B9 (VBUS)
/RP_BOOT: R5.2, SW2.1, SW2.2
/RP_MATRIX_C0: U1.78 (GPIO1), U5.C1
/RP_MATRIX_C1: U1.77 (GPIO0), U5.C2
/RP_MATRIX_C2: U1.58 (GPIO47/ADC7), U5.C3
/RP_MATRIX_C3: U1.57 (GPIO46/ADC6), U5.C4
/RP_MATRIX_C4: U1.56 (GPIO45/ADC5), U5.C5
/RP_MATRIX_C5: U1.55 (GPIO44/ADC4), U5.C6
/RP_MATRIX_C6: U1.54 (GPIO43/ADC3), U5.C7
/RP_MATRIX_C7: U1.53 (GPIO42/ADC2), U5.C8
/RP_MATRIX_C8: U1.52 (GPIO41/ADC1), U5.C9
/RP_MATRIX_C9: U1.49 (GPIO40/ADC0), U5.C10
/RP_MATRIX_C10: U1.48 (GPIO39), U5.C11
/RP_MATRIX_C11: U1.47 (GPIO38), U5.C12
/RP_MATRIX_C12: U1.46 (GPIO37), U5.C13
/RP_MATRIX_C13: U1.45 (GPIO36), U5.C14
/RP_MATRIX_C14: U1.44 (GPIO35), U5.C15
/RP_MATRIX_C15: U1.43 (GPIO34), U5.C16
/RP_MATRIX_C16: U1.42 (GPIO33), U5.C17
/RP_MATRIX_C17: U1.40 (GPIO32), U5.C18
/RP_MATRIX_C18: U1.39 (GPIO31), U5.C19
/RP_MATRIX_C19: U1.38 (GPIO30), U5.C20
/RP_MATRIX_C20: U1.37 (GPIO29), U5.C21
/RP_MATRIX_C21: U1.36 (GPIO28), U5.C22
/RP_MATRIX_R0: U1.17 (GPIO17), U5.R1
/RP_MATRIX_R1: U1.18 (GPIO18), U5.R2
/RP_MATRIX_R2: U1.19 (GPIO19), U5.R3
/RP_MATRIX_R3: U1.20 (GPIO20), U5.R4
/RP_MATRIX_R4: U1.21 (GPIO21), U5.R5
/RP_MATRIX_R5: U1.22 (GPIO22), U5.R6
/RP_RGB0: U1.4 (GPIO7), U3.5 (2A)
/RP_RGB0_5V: U3.6 (2Y), U5.L1
/RP_RGB1: U1.3 (GPIO6), U3.2 (1A)
/RP_RGB1_5V: U3.3 (1Y), U5.L2
/RP_RGB2: U1.2 (GPIO5), U6.12 (4A)
/RP_RGB2_5V: U5.L3, U6.11 (4Y)
/RP_RGB3: U1.1 (GPIO4), U6.9 (3A)
/RP_RGB3_5V: U5.L4, U6.8 (3Y)
/RP_RGB4: U1.80 (GPIO3), U6.5 (2A)
/RP_RGB4_5V: U5.L5, U6.6 (2Y)
/RP_RGB5: U1.79 (GPIO2), U6.2 (1A)
/RP_RGB5_5V: U5.L6, U6.3 (1Y)
/RP_RST: R2.1, SW1.1, SW1.2
/RP_SCLK: U1.7 (GPIO9), U3.12 (4A)
/RP_SCLK_5V: U3.11 (4Y), U5.SL
/RP_SDAT: U1.8 (GPIO10), U3.9 (3A)
/RP_SDAT_5V: U3.8 (3Y), U5.SD
/RP_SWCLK: U1.33 (SWCLK), U13.1
/RP_SWDIO: U1.34 (SWDIO), U13.3
/RP_USB_D_D+: R4.2, U1.67 (USB_DP)
/RP_USB_D_D-: R3.2, U1.66 (USB_DM)
/RP_USB_P_D+: R4.1, USB1.A6 (D+), USB1.B6 (D+)
/RP_USB_P_D-: R3.1, USB1.A7 (D-), USB1.B7 (D-)
/RP_VREG_AVDD: C1.1, R1.1, U1.61 (VREG_AVDD)
/RP_VREG_LX: L1.1, U1.63 (VREG_LX)
/RP_XIN: C12.1, OSC1.1, U1.30 (XIN)
/RP_XOUT: R6.1, U1.31 (XOUT)
GND: C1.2, C2.2, C3.2, C4.2, C5.1, C6.2, C7.2, C8.2, C9.2, C10.2, C11.2, C12.2, C13.2, C14.2, C15.2, C16.2, C17.2, C18.2, C19.2, C20.2, C21.2, C41.2, C42.2, C43.2, OSC1.2 (GND), OSC1.4 (GND), SW1.3, SW1.4, SW2.3, SW2.4, U1.62 (VREG_PGND), U1.81 (GND), U3.1 (~1OE), U3.4 (~2OE), U3.7 (GND), U3.10 (~3OE), U3.13 (~4OE), U3.15 (GND), U4.4 (GND), U5.VSS, U6.1 (~1OE), U6.4 (~2OE), U6.7 (GND), U6.10 (~3OE), U6.13 (~4OE), U6.15 (GND), U13.2, U13.4, U13.5, USB1.1, USB1.2, USB1.3, USB1.4, USB1.A1 (GND), USB1.A12 (GND), USB1.B1 (GND), USB1.B12 (GND)
unnamed: C5.2, OSC1.3, R6.2
unnamed: R2.2, U1.35 (RUN)
unnamed: R5.1, U1.75 (~QSPI_SS)
unnamed: C22.2, U4.6 (BST)
unnamed: C22.1, L2.2, U4.5 (SW)

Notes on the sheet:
3V3 BUCK
USB CONNECTOR

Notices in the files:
schem/KeyboardV2.kicad_pcb:
© 2026, Thomas Kasper
